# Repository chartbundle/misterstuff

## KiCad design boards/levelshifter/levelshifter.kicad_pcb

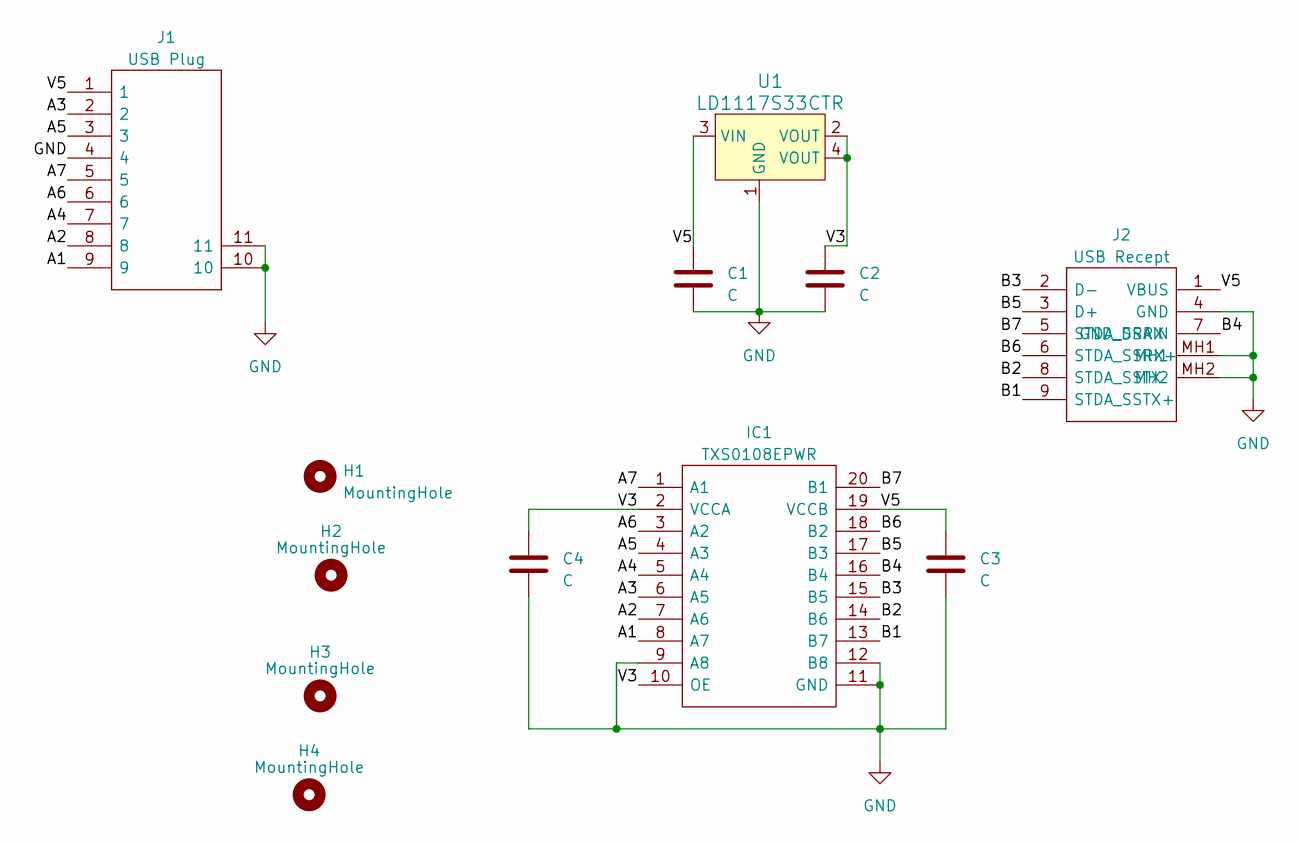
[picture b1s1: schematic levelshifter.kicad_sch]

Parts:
C1, C2, C3, C4: C; C_0805_2012Metric
H1, H2, H3, H4: MountingHole; MountingHole_2.2mm_M2
IC1: TXS0108EPWR; SOP65P640X120-20N; Manufacturer_Part_Number TXS0108EPWR; Mouser Part Number 595-TXS0108EPWR
J1: USB Plug; 692112030100; Mouser2 Part Number 710-692112030100
J2: USB Recept; 692122030100; Mouser2 Part Number 710-692122030100
U1: LD1117S33CTR; SOT-223; MPN LD1117S33CTR; Digi-Key_PN 497-1241-1-ND

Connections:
/A1: IC1.8 (A7), J1.9
/A2: IC1.7 (A6), J1.8
/A3: IC1.6 (A5), J1.2
/A4: IC1.5 (A4), J1.7
/A5: IC1.4 (A3), J1.3
/A6: IC1.3 (A2), J1.6
/A7: IC1.1 (A1), J1.5
/B1: IC1.13 (B7), J2.9 (STDA_SSTX+)
/B2: IC1.14 (B6), J2.8 (STDA_SSTX)
/B3: IC1.15 (B5), J2.2 (D-)
/B4: IC1.16 (B4), J2.7 (GND_DRAIN)
/B5: IC1.17 (B3), J2.3 (D+)
/B6: IC1.18 (B2), J2.6 (STDA_SSRX+)
/B7: IC1.20 (B1), J2.5 (STDA_SSRX)
/V3: C2.1, C4.1, IC1.2 (VCCA), IC1.10 (OE), U1.2 (VOUT), U1.4 (VOUT)
/V5: C1.1, C3.1, IC1.19 (VCCB), J1.1, J2.1 (VBUS), U1.3 (VIN)
GND: C1.2, C2.2, C3.2, C4.2, IC1.9 (A8), IC1.11 (GND), IC1.12 (B8), J1.4, J1.10, J1.11, J2.4 (GND), J2.MH1, J2.MH2, U1.1 (GND)

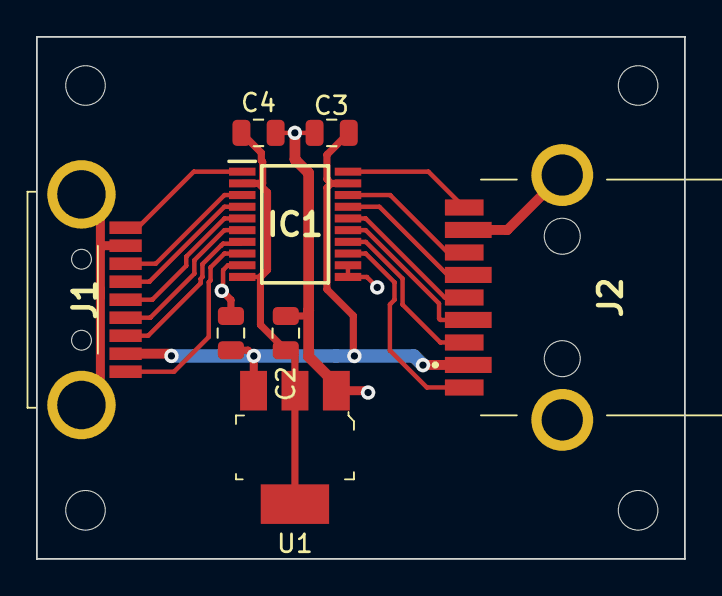
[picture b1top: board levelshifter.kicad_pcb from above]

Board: 2 copper layers, 36.0 x 29.0 mm, 12 parts (0 on the bottom side), 17 nets.

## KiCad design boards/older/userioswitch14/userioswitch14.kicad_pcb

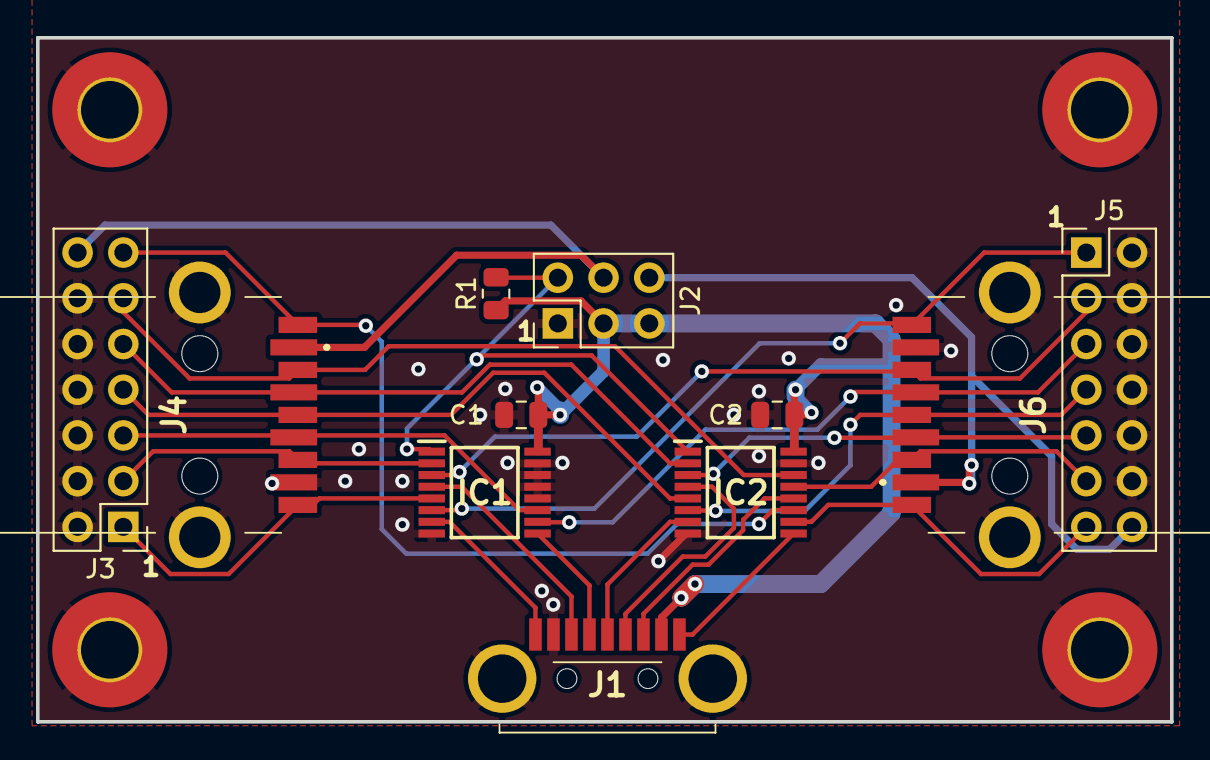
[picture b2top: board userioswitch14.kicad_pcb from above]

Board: 2 copper layers, 63.0 x 38.0 mm, 15 parts (0 on the bottom side), 26 nets.

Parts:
C1, C2: 10u; C_0805_2012Metric
H1, H2, H3, H4: M3; MountingHole_3.2mm_M3_Pad_TopBottom
IC1, IC2: SN3257QPWRQ1; SOP65P640X120-16N
J1: 692112030100; 692112030100-fixed
J2: 2x03; PinHeader_2x03_P2.54mm_Vertical
J3, J5: Header; PinHeader_2x07_P2.54mm_Vertical
J4, J6: 692122030100
R1: 4K7; R_0805_2012Metric

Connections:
/D1: IC2.4 (D1), J1.2
/D2: IC1.9 (D3), J1.3
/D3: IC1.7 (D2), J1.5
/D4: IC1.4 (D1), J1.6
/D5: IC2.7 (D2), J1.7
/D6: IC2.12 (D4), J1.8
/D7: IC2.9 (D3), J1.9
/S1A: IC2.2 (S1A), J3.9, J4.2 (D-)
/S1B: IC2.3 (S1B), J5.9, J6.2 (D-)
/S2A: IC1.11 (S3A), J3.5, J4.3 (D+)
/S2B: IC1.10 (S3B), J5.5, J6.3 (D+)
/S3A: IC1.5 (S2A), J3.1, J4.5 (STDA_SSRX)
/S3B: IC1.6 (S2B), J5.1, J6.5 (STDA_SSRX)
/S4A: IC1.2 (S1A), J3.3, J4.6 (STDA_SSRX+)
/S4B: IC1.3 (S1B), J5.3, J6.6 (STDA_SSRX+)
/S5A: IC2.5 (S2A), J3.7, J4.7 (GND_DRAIN)
/S5B: IC2.6 (S2B), J5.7, J6.7 (GND_DRAIN)
/S6A: IC2.14 (S4A), J3.11, J4.8 (STDA_SSTX)
/S6B: IC2.13 (S4B), J5.11, J6.8 (STDA_SSTX)
/S7A: IC2.11 (S3A), J3.13, J4.9 (STDA_SSTX+)
/S7B: IC2.10 (S3B), J5.13, J6.9 (STDA_SSTX+)
/SEL: IC1.1 (SEL), IC2.1 (SEL), J2.2, R1.2
/VBUSA: J2.4, J3.14, J4.1 (VBUS)
/VBUSB: J2.6, J5.14, J6.1 (VBUS)
GND: C1.2, C2.2, H1.1, H2.1, H3.1, H4.1, IC1.8 (GND), IC1.12 (D4), IC1.13 (S4B), IC1.14 (S4A), IC1.15 (~EN), IC2.8 (GND), IC2.15 (~EN), J1.4, J1.10, J1.11, J2.1, J3.2, J3.4, J3.6, J3.8, J3.10, J3.12, J4.4 (GND), J4.MH1, J4.MH2, J5.2, J5.4, J5.6, J5.8, J5.10, J5.12, J6.4 (GND), J6.MH1, J6.MH2
VBUS: C1.1, C2.1, IC1.16 (VDD), IC2.16 (VDD), J1.1, J2.3, J2.5, R1.1
